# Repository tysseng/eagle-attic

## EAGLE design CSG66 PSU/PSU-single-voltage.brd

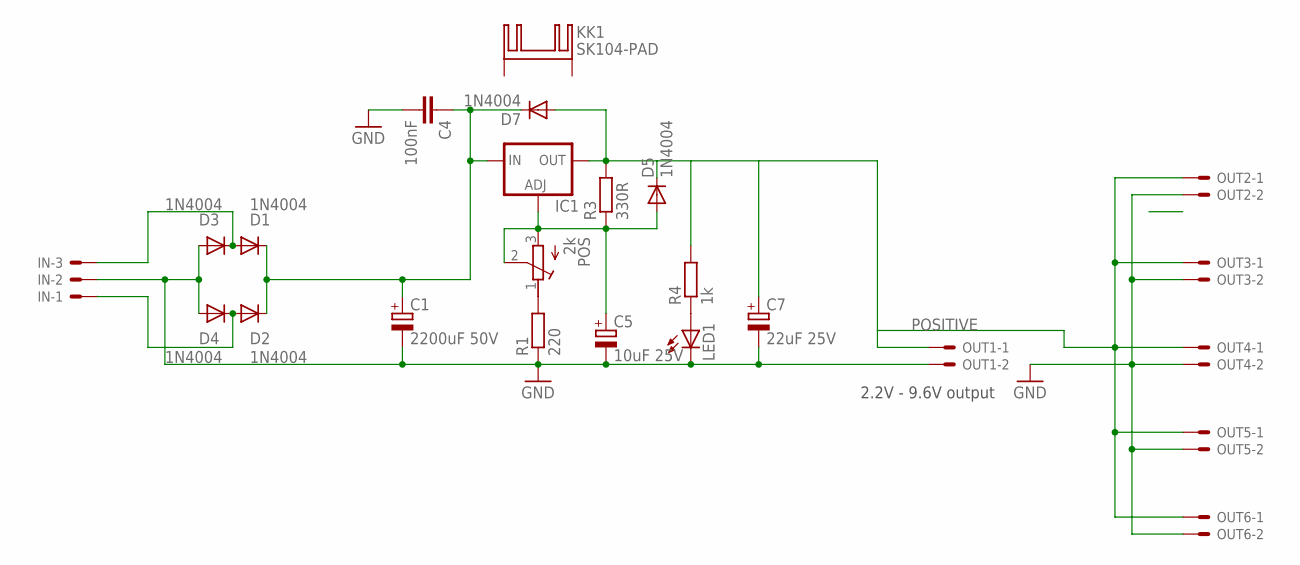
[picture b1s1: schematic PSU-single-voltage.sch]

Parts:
C1: 2200uF 50V; E7,5-16
C4: 100nF; C050-025X075
C5: 10uF 25V; E2,5-5
C7: 22uF 25V; E2,5-5
D1, D2, D3, D4, D5, D7: 1N4004; DO41-10
IC1: LM317TS; 317TS
IN: KK-156-3
KK1: SK104-PAD
LED1: LED3MM
OUT1, OUT2, OUT3, OUT4, OUT5, OUT6: KK-156-2
POS: 2k; RTRIMT93YA
R1: 220; 0207/7
R3: 330R; 0207/7
R4: 1k; 0207/7

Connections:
GND: C1.-, C4.2, C5.-, C7.-, D3.A, D4.A, IN.2, LED1.K (C), OUT1.2, OUT2.2, OUT3.2, OUT4.2, OUT5.2, OUT6.2, R1.1
unnamed: D2.A, D4.C, IN.1
unnamed: LED1.A, R4.1
unnamed: POS.1 (E), R1.2
unnamed: C5.+, D5.A, IC1.1 (ADJ), POS.2 (S), POS.3 (A), R3.1
unnamed: C1.+, C4.1, D1.C, D2.C, D7.C, IC1.3 (IN)
unnamed: D1.A, D3.C, IN.3
POSITIVE: C7.+, D5.C, D7.A, IC1.2 (OUT), OUT1.1, OUT2.1, OUT3.1, OUT4.1, OUT5.1, OUT6.1, R3.2, R4.2

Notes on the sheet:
2.2V - 9.6V output

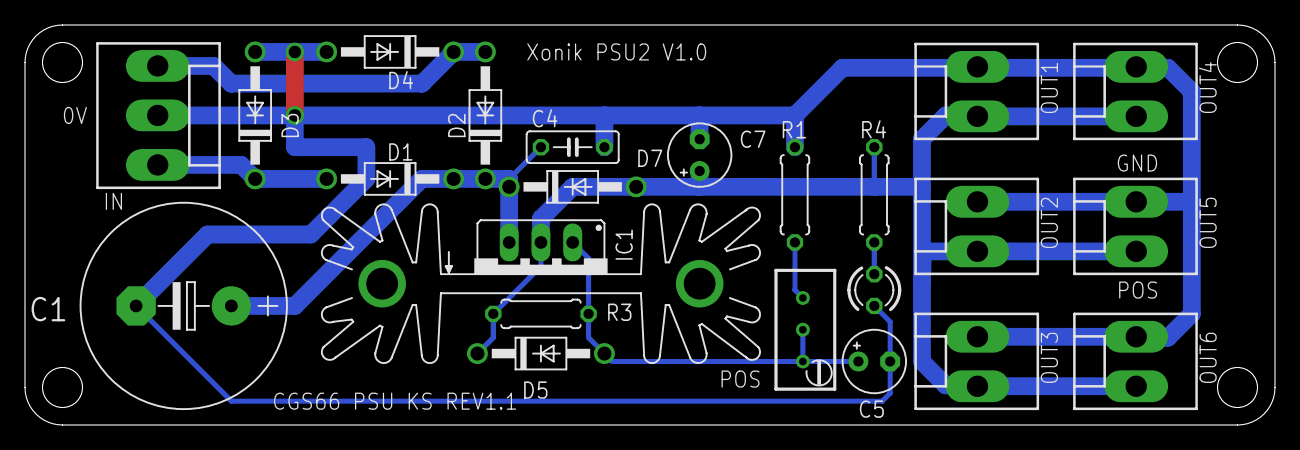
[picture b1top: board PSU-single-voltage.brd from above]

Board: 2 copper layers, 100.0 x 32.0 mm, 24 parts (0 on the bottom side), 8 nets.

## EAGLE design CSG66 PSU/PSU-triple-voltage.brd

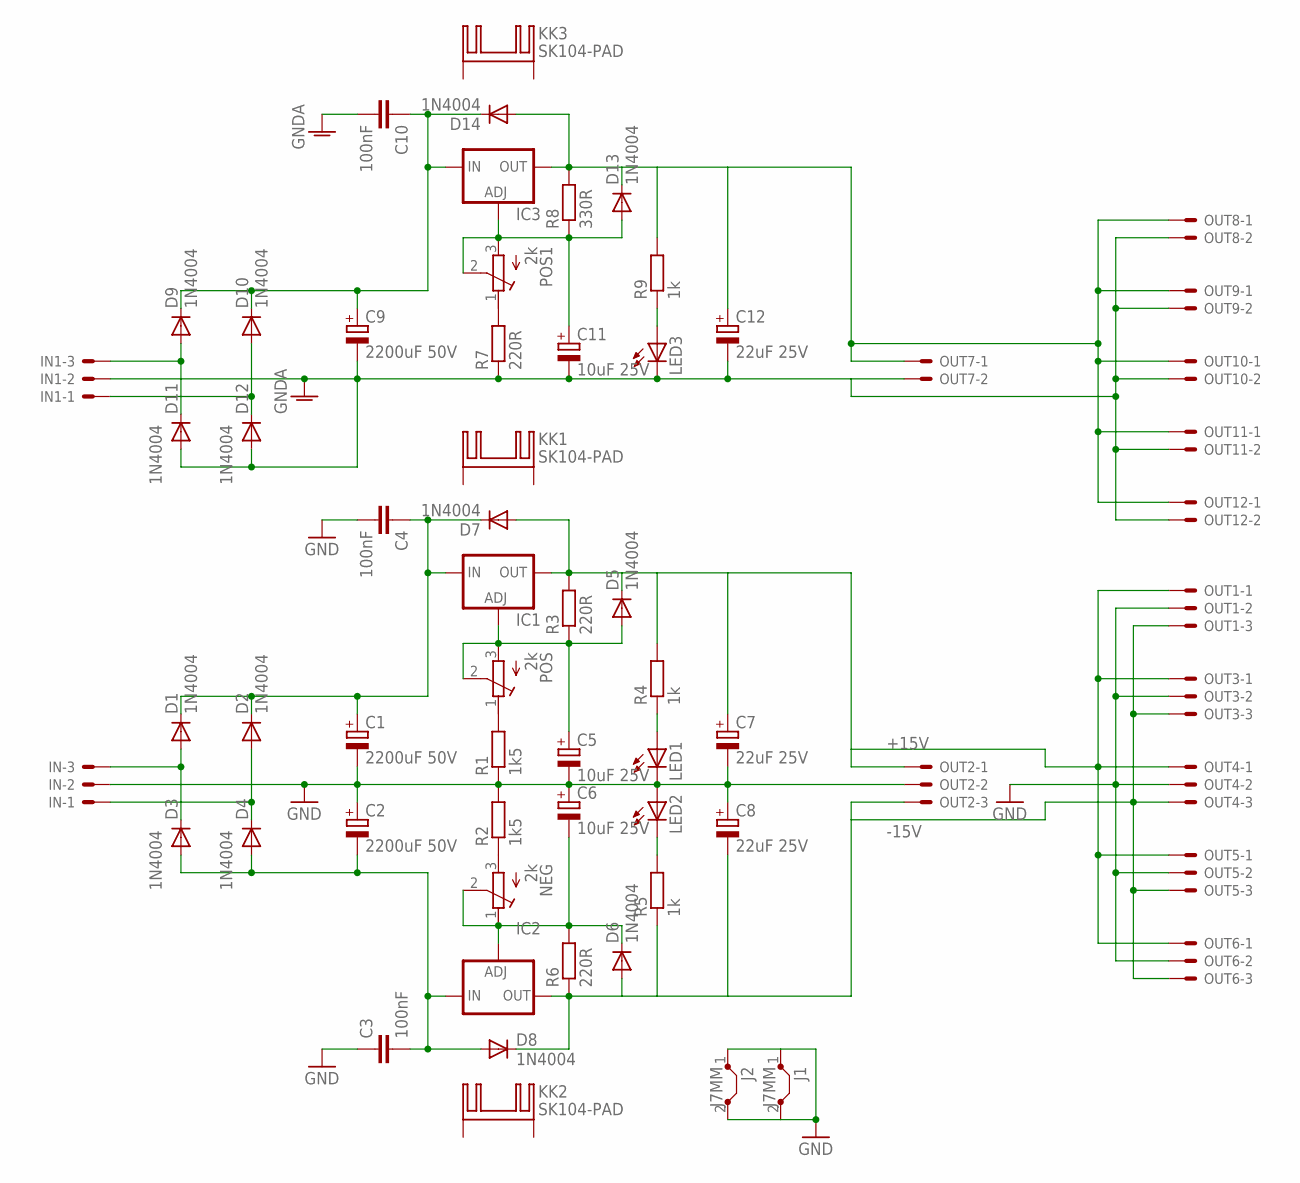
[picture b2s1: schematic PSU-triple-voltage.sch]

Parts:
C1, C2, C9: 2200uF 50V; E7,5-16
C3, C4, C10: 100nF; C050-025X075
C5, C6, C11: 10uF 25V; E2,5-5
C7, C8, C12: 22uF 25V; E2,5-5
D1, D2, D3, D4, D5, D6, D7, D8, D9, D10, D11, D12, D13, D14: 1N4004; DO41-10
IC1, IC3: LM317TS; 317TS
IC2: LM337TS; 337TS
IN, IN1: KK-156-3
J1, J2: J7MM; 07
KK1, KK2, KK3: SK104-PAD
LED1, LED2, LED3: LED3MM
NEG: 2k; RTRIMT93YA
OUT1, OUT2, OUT3, OUT4, OUT5, OUT6: KK-156-3
OUT7, OUT8, OUT9, OUT10, OUT11, OUT12: KK-156-2
POS, POS1: 2k; RTRIMT93YA
R1, R2: 1k5; 0207/7
R3, R6, R7: 220R; 0207/7
R4, R5, R9: 1k; 0207/7
R8: 330R; 0207/7

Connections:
+5V: C12.+, D13.C, D14.A, IC3.2 (OUT), OUT7.1, OUT8.1, OUT9.1, OUT10.1, OUT11.1, OUT12.1, R8.2, R9.2
+15V: C7.+, D5.C, D7.A, IC1.2 (OUT), OUT1.1, OUT2.1, OUT3.1, OUT4.1, OUT5.1, OUT6.1, R3.2, R4.2
-15V: C8.-, D6.A, D8.C, IC2.3 (OUT), OUT1.3, OUT2.3, OUT3.3, OUT4.3, OUT5.3, OUT6.3, R5.1, R6.1
GND: C1.-, C2.+, C3.1, C4.2, C5.-, C6.+, C7.-, C8.+, IN.2, J1.1, J1.2, J2.1, J2.2, LED1.K (C), LED2.A, OUT1.2, OUT2.2, OUT3.2, OUT4.2, OUT5.2, OUT6.2, R1.1, R2.2
GNDA: C9.-, C10.2, C11.-, C12.-, D11.A, D12.A, IN1.2, LED3.K (C), OUT7.2, OUT8.2, OUT9.2, OUT10.2, OUT11.2, OUT12.2, R7.1
unnamed: LED3.A, R9.1
unnamed: POS1.1 (E), R7.2
unnamed: C11.+, D13.A, IC3.1 (ADJ), POS1.2 (S), POS1.3 (A), R8.1
unnamed: LED1.A, R4.1
unnamed: C9.+, C10.1, D9.C, D10.C, D14.C, IC3.3 (IN)
unnamed: LED2.K (C), R5.2
unnamed: D10.A, D12.C, IN1.1
unnamed: POS.1 (E), R1.2
unnamed: C5.+, D5.A, IC1.1 (ADJ), POS.2 (S), POS.3 (A), R3.1
unnamed: NEG.3 (A), R2.1
unnamed: C6.-, D6.C, IC2.1 (ADJ), NEG.1 (E), NEG.2 (S), R6.2
unnamed: C2.-, C3.2, D3.A, D4.A, D8.A, IC2.2 (IN)
unnamed: D9.A, D11.C, IN1.3
unnamed: C1.+, C4.1, D1.C, D2.C, D7.C, IC1.3 (IN)
unnamed: D2.A, D4.C, IN.1
unnamed: D1.A, D3.C, IN.3

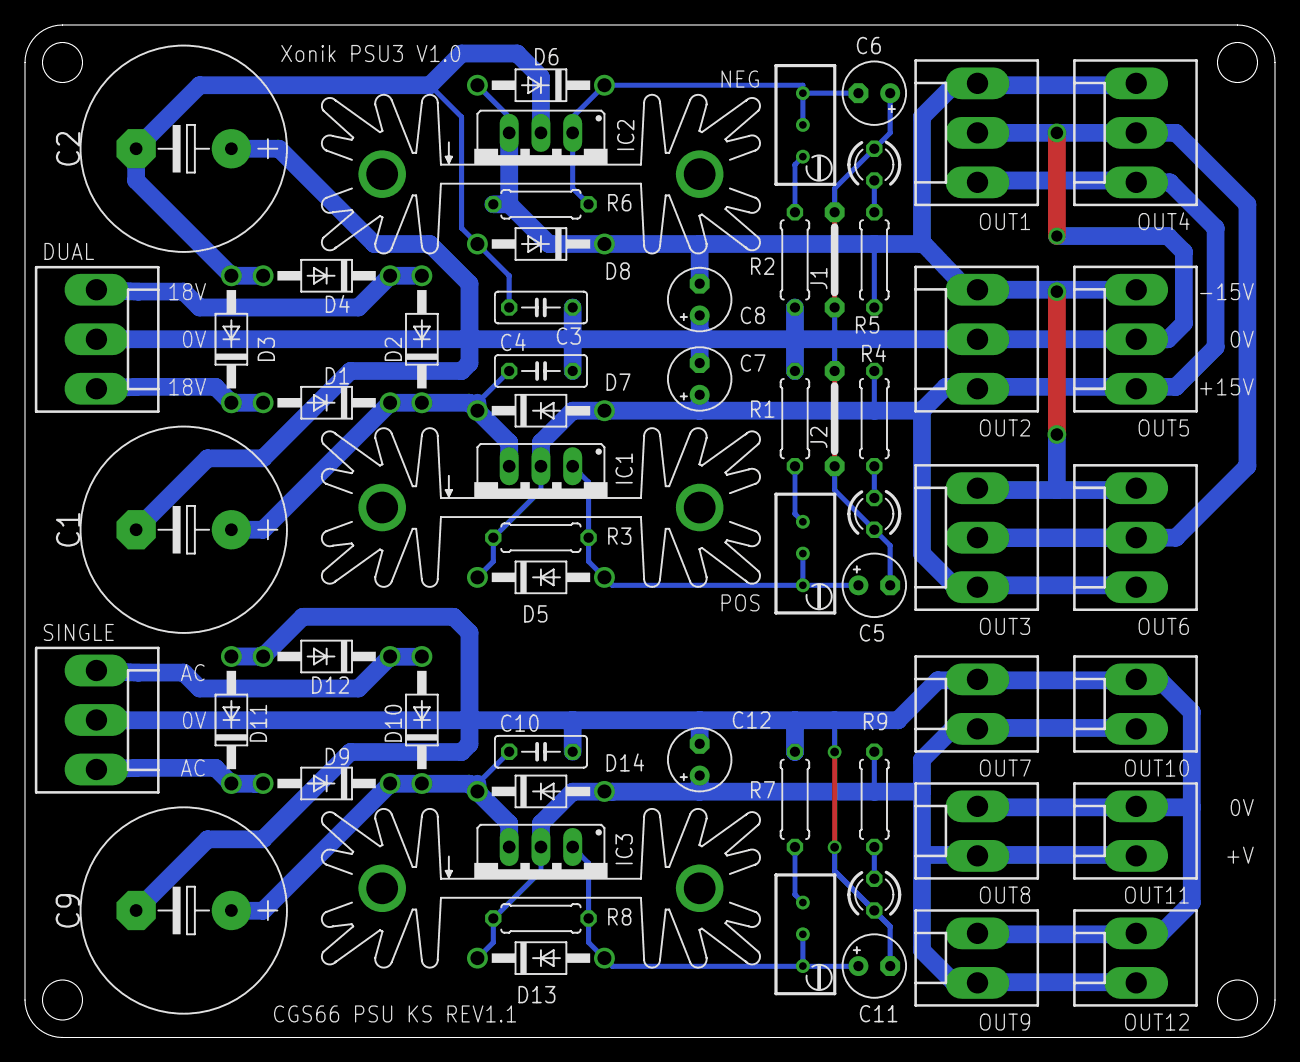
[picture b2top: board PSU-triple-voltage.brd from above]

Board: 2 copper layers, 100.0 x 81.0 mm, 63 parts (0 on the bottom side), 21 nets.

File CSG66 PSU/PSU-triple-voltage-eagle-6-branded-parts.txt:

Partlist

Exported from PSU-triple-voltage-eagle-6-branded.sch at 01.03.2015 13:05:13

EAGLE Version 6.2.0 Copyright (c) 1988-2012 CadSoft

Assembly variant: 

Part     Value          Device          Package      Library   Sheet

C1       2200uF 50V     CPOL-EUE7.5-16  E7,5-16      resistor  1
C2       2200uF 50V     CPOL-EUE7.5-16  E7,5-16      resistor  1
C3       100nF          C-EU050-025X075 C050-025X075 resistor  1
C4       100nF          C-EU050-025X075 C050-025X075 resistor  1
C5       10uF 25V       CPOL-EUE2.5-5   E2,5-5       resistor  1
C6       10uF 25V       CPOL-EUE2.5-5   E2,5-5       resistor  1
C7       22uF 25V       CPOL-EUE2.5-5   E2,5-5       resistor  1
C8       22uF 25V       CPOL-EUE2.5-5   E2,5-5       resistor  1
C9       2200uF 50V     CPOL-EUE7.5-16  E7,5-16      resistor  1
C10      100nF          C-EU050-025X075 C050-025X075 resistor  1
C11      10uF 25V       CPOL-EUE2.5-5   E2,5-5       resistor  1
C12      22uF 25V       CPOL-EUE2.5-5   E2,5-5       resistor  1
D1       1N4004         1N4004          DO41-10      diode     1
D2       1N4004         1N4004          DO41-10      diode     1
D3       1N4004         1N4004          DO41-10      diode     1
D4       1N4004         1N4004          DO41-10      diode     1
D5       1N4004         1N4004          DO41-10      diode     1
D6       1N4004         1N4004          DO41-10      diode     1
D7       1N4004         1N4004          DO41-10      diode     1
D8       1N4004         1N4004          DO41-10      diode     1
D9       1N4004         1N4004          DO41-10      diode     1
D10      1N4004         1N4004          DO41-10      diode     1
D11      1N4004         1N4004          DO41-10      diode     1
D12      1N4004         1N4004          DO41-10      diode     1
D13      1N4004         1N4004          DO41-10      diode     1
D14      1N4004         1N4004          DO41-10      diode     1
IC1                     LM317TS         317TS        v-reg     1
IC2                     LM337TS         337TS        v-reg     1
IC3                     LM317TS         317TS        v-reg     1
IN                      KK-156-3        KK-156-3     con-molex 1
IN1                     KK-156-3        KK-156-3     con-molex 1
KK1      SK104-PAD      SK104-PAD       SK104-PAD    heatsink  1
KK2      SK104-PAD      SK104-PAD       SK104-PAD    heatsink  1
KK3      SK104-PAD      SK104-PAD       SK104-PAD    heatsink  1
LED1                    LED3MM          LED3MM       led       1
LED2                    LED3MM          LED3MM       led       1
LED3                    LED3MM          LED3MM       led       1
NEG      2k             R-TRIMMT93YA    RTRIMT93YA   resistor  1
OUT1                    KK-156-3        KK-156-3     con-molex 1
OUT2                    KK-156-3        KK-156-3     con-molex 1
OUT3                    KK-156-3        KK-156-3     con-molex 1
OUT4                    KK-156-3        KK-156-3     con-molex 1
OUT5                    KK-156-3        KK-156-3     con-molex 1
OUT6                    KK-156-3        KK-156-3     con-molex 1
OUT7                    KK-156-2        KK-156-2     con-molex 1
OUT8                    KK-156-2        KK-156-2     con-molex 1
OUT9                    KK-156-2        KK-156-2     con-molex 1
OUT10                   KK-156-2        KK-156-2     con-molex 1
OUT11                   KK-156-2        KK-156-2     con-molex 1
OUT12                   KK-156-2        KK-156-2     con-molex 1
POS      2k             R-TRIMMT93YA    RTRIMT93YA   resistor  1
POS1     2k             R-TRIMMT93YA    RTRIMT93YA   resistor  1
R1       1k5            R-EU_0207/7     0207/7       resistor  1
R2       1k5            R-EU_0207/7     0207/7       resistor  1
R3       220R           R-EU_0207/7     0207/7       resistor  1
R4       1k             R-EU_0207/7     0207/7       resistor  1
R5       1k             R-EU_0207/7     0207/7       resistor  1
R6       220R           R-EU_0207/7     0207/7       resistor  1
R7       220R           R-EU_0207/7     0207/7       resistor  1
R8       330R           R-EU_0207/7     0207/7       resistor  1
R9       1k             R-EU_0207/7     0207/7       resistor  1

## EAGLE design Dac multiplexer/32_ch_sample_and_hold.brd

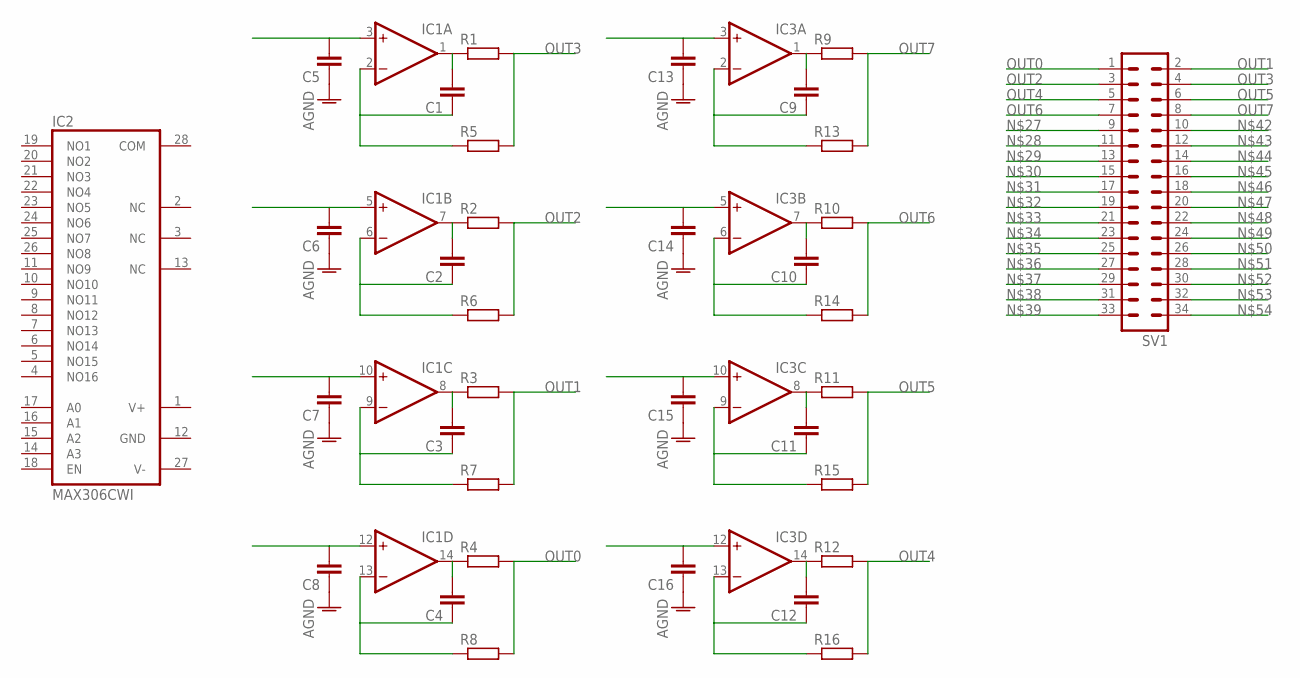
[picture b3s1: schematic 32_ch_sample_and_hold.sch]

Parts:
C1, C2, C3, C4, C9, C10, C11, C12: C-EUC0603; C0603
C5, C6, C7, C8, C13, C14, C15, C16: C-EUC1206; C1206
IC1, IC3: TL074D; SO14
IC2: MAX306CWI; SO28L
R1, R2, R3, R4, R5, R6, R7, R8, R9, R10, R11, R12, R13, R14, R15, R16: R-EU_R0603; R0603
SV1: MA17-2

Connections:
AGND: C5.1, C6.1, C7.1, C8.1, C13.1, C14.1, C15.1, C16.1
GND: IC2.12 (GND)
unnamed: C1.2, IC1.1 (OUT), R1.1
unnamed: C2.2, IC1.7 (OUT), R2.1
unnamed: C3.2, IC1.8 (OUT), R3.1
unnamed: C4.2, IC1.14 (OUT), R4.1
unnamed: C1.1, IC1.2 (-IN), R5.1
unnamed: C2.1, IC1.6 (-IN), R6.1
unnamed: C3.1, IC1.9 (-IN), R7.1
unnamed: C4.1, IC1.13 (-IN), R8.1
unnamed: C9.2, IC3.1 (OUT), R9.1
unnamed: C10.2, IC3.7 (OUT), R10.1
unnamed: C11.2, IC3.8 (OUT), R11.1
unnamed: C12.2, IC3.14 (OUT), R12.1
unnamed: C8.2, IC1.12 (+IN)
unnamed: C7.2, IC1.10 (+IN)
unnamed: C6.2, IC1.5 (+IN)
unnamed: C5.2, IC1.3 (+IN)
unnamed: C9.1, IC3.2 (-IN), R13.1
unnamed: C10.1, IC3.6 (-IN), R14.1
unnamed: C11.1, IC3.9 (-IN), R15.1
unnamed: C12.1, IC3.13 (-IN), R16.1
unnamed: C16.2, IC3.12 (+IN)
unnamed: C15.2, IC3.10 (+IN)
unnamed: C14.2, IC3.5 (+IN)
unnamed: C13.2, IC3.3 (+IN)
OUT0: R4.2, R8.2, SV1.1
OUT1: R3.2, R7.2, SV1.2
OUT2: R2.2, R6.2, SV1.3
OUT3: R1.2, R5.2, SV1.4
OUT4: R12.2, R16.2, SV1.5
OUT5: R11.2, R15.2, SV1.6
OUT6: R10.2, R14.2, SV1.7
OUT7: R9.2, R13.2, SV1.8
V+: IC1.4 (V+), IC2.1 (V+), IC3.4 (V+)
V-: IC1.11 (V-), IC2.27 (V-), IC3.11 (V-)

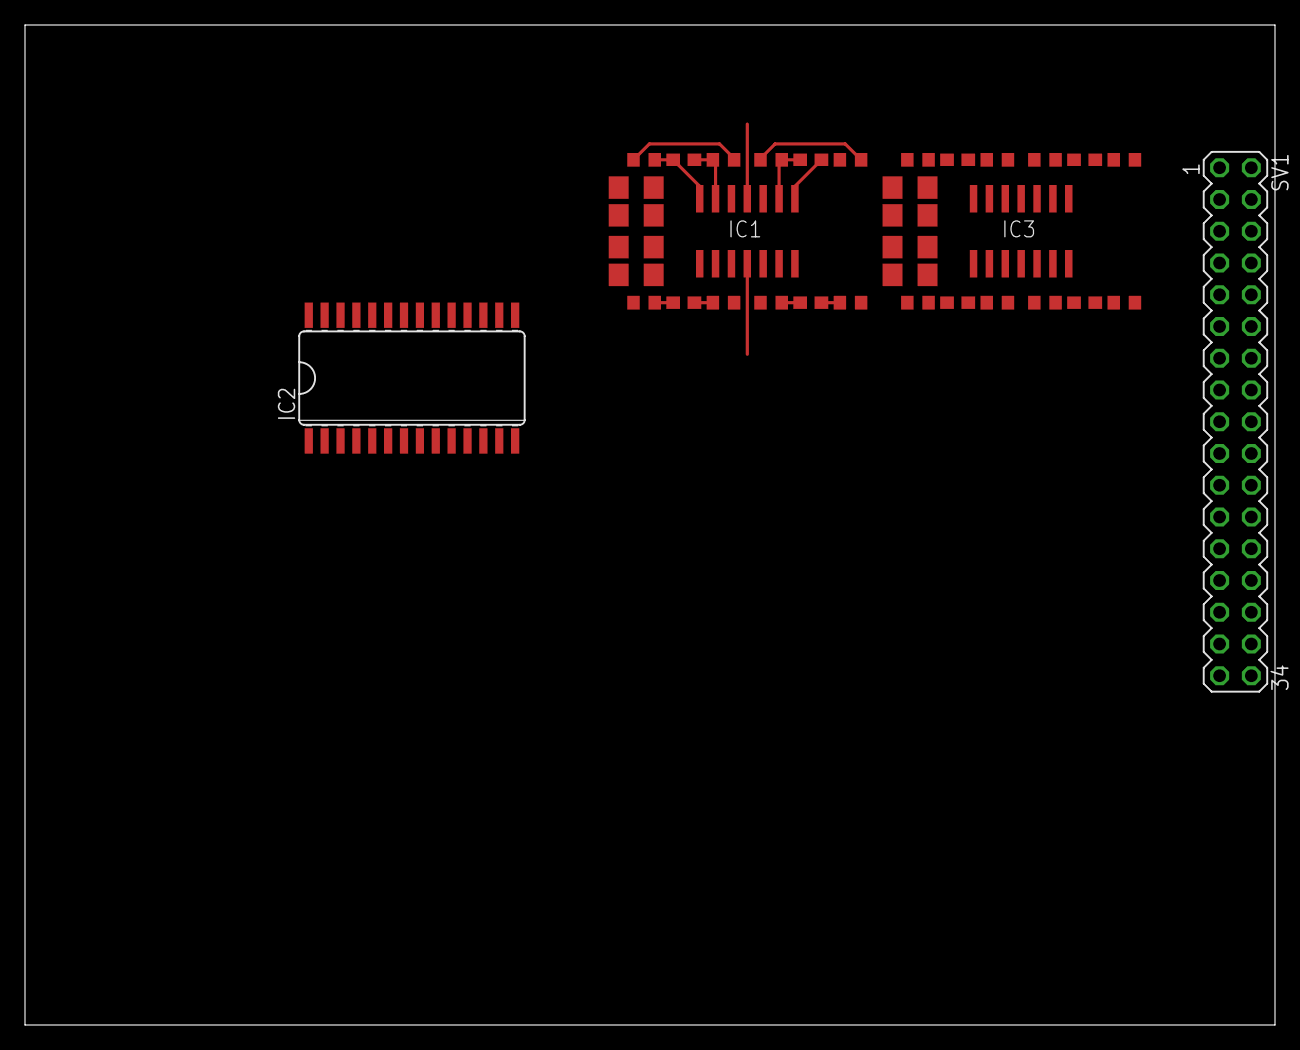
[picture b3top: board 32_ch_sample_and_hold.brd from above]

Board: 2 copper layers, 100.0 x 80.0 mm, 36 parts (0 on the bottom side), 35 nets.

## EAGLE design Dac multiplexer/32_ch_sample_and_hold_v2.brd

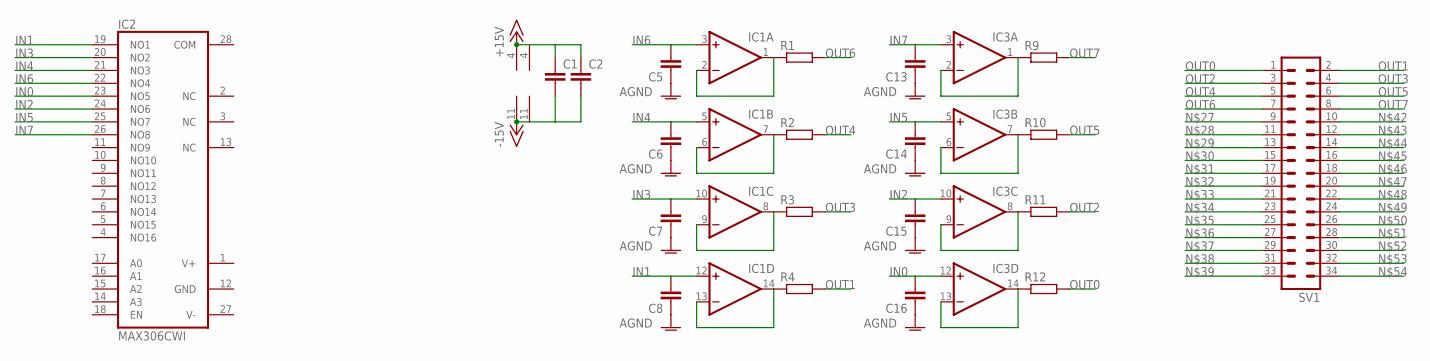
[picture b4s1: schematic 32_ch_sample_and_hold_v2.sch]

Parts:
C1, C2: C-EUC0603; C0603
C5, C6, C7, C8, C13, C14, C15, C16: C-EUC1206; C1206
IC1, IC3: TL074D; SO14
IC2: MAX306CWI; SO28L
R1, R2, R3, R4, R9, R10, R11, R12: R-EU_R0603; R0603
SV1: MA17-2

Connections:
+15V: C1.1, C2.1, IC1.4 (V+), IC3.4 (V+)
-15V: C1.2, C2.2, IC1.11 (V-), IC3.11 (V-)
AGND: C5.1, C6.1, C7.1, C8.1, C13.1, C14.1, C15.1, C16.1
GND: IC2.12 (GND)
IN0: C16.2, IC2.23 (NO5), IC3.12 (+IN)
IN1: C8.2, IC1.12 (+IN), IC2.19 (NO1)
IN2: C15.2, IC2.24 (NO6), IC3.10 (+IN)
IN3: C7.2, IC1.10 (+IN), IC2.20 (NO2)
IN4: C6.2, IC1.5 (+IN), IC2.21 (NO3)
IN5: C14.2, IC2.25 (NO7), IC3.5 (+IN)
IN6: C5.2, IC1.3 (+IN), IC2.22 (NO4)
IN7: C13.2, IC2.26 (NO8), IC3.3 (+IN)
unnamed: IC1.1 (OUT), IC1.2 (-IN), R1.1
unnamed: IC1.6 (-IN), IC1.7 (OUT), R2.1
unnamed: IC1.8 (OUT), IC1.9 (-IN), R3.1
unnamed: IC1.13 (-IN), IC1.14 (OUT), R4.1
unnamed: IC3.1 (OUT), IC3.2 (-IN), R9.1
unnamed: IC3.6 (-IN), IC3.7 (OUT), R10.1
unnamed: IC3.8 (OUT), IC3.9 (-IN), R11.1
unnamed: IC3.13 (-IN), IC3.14 (OUT), R12.1
OUT0: R12.2, SV1.1
OUT1: R4.2, SV1.2
OUT2: R11.2, SV1.3
OUT3: R3.2, SV1.4
OUT4: R2.2, SV1.5
OUT5: R10.2, SV1.6
OUT6: R1.2, SV1.7
OUT7: R9.2, SV1.8
V+: IC2.1 (V+)
V-: IC2.27 (V-)

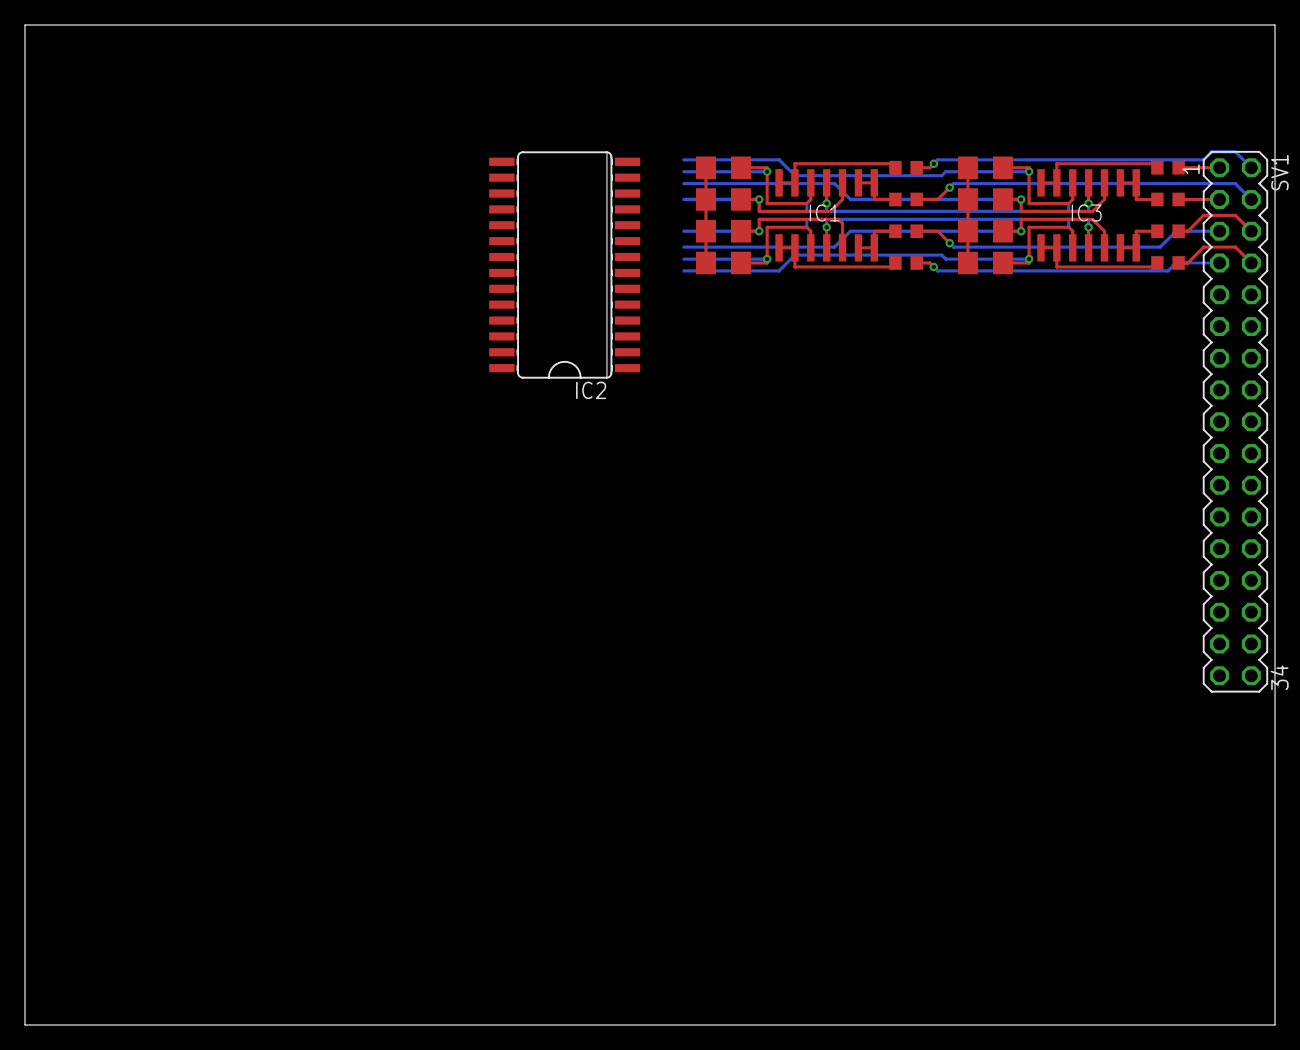
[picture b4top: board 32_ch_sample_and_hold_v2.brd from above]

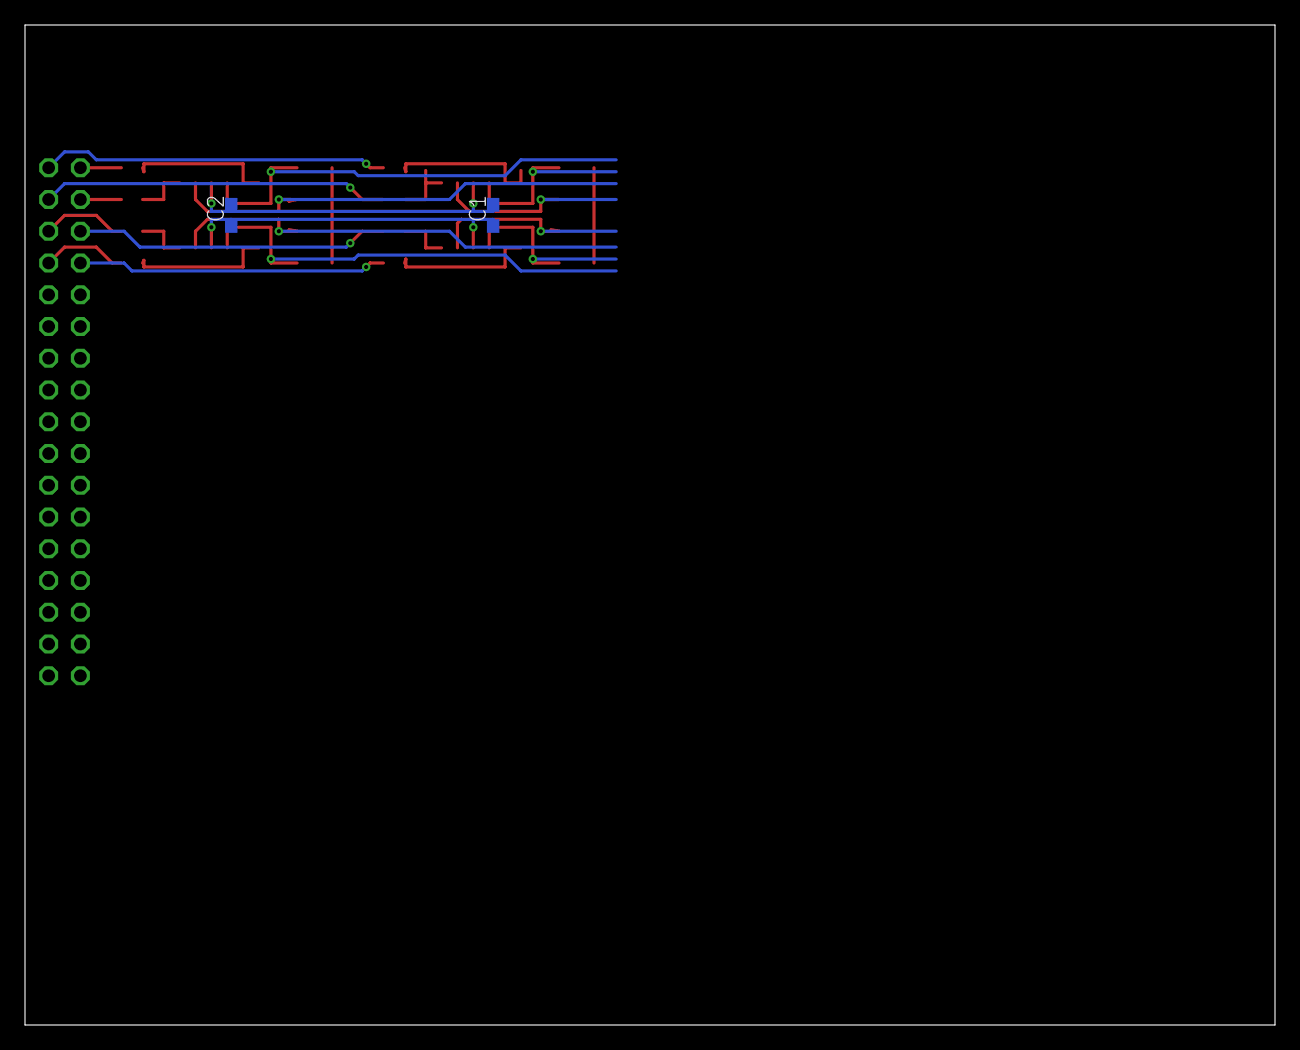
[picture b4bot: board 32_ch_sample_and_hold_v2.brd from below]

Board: 2 copper layers, 100.0 x 80.0 mm, 22 parts (2 on the bottom side), 27 nets.

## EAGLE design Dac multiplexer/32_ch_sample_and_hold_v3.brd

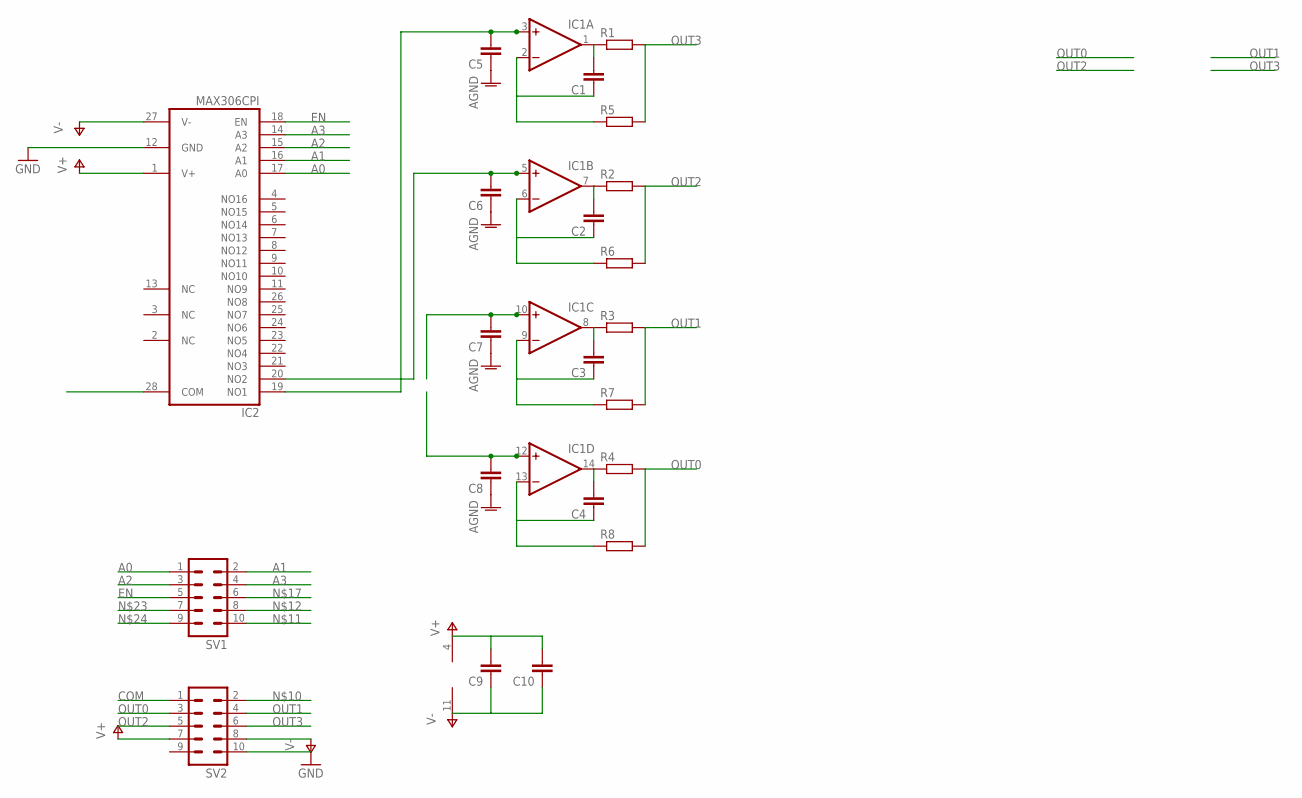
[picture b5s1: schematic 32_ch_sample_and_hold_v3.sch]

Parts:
C1, C2, C3, C4, C5, C6, C7, C8, C9, C10: C-EU025-025X050; C025-025X050
IC1: TL074P; DIL14
IC2: MAX306CPI; DIL28-6
R1, R2, R3, R4, R5, R6, R7, R8: R-EU_0207/7; 0207/7
SV1, SV2: MA05-2

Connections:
A0: IC2.17 (A0), SV1.1
A1: IC2.16 (A1), SV1.2
A2: IC2.15 (A2), SV1.3
A3: IC2.14 (A3), SV1.4
AGND: C5.1, C6.1, C7.1, C8.1
COM: IC2.28 (COM), SV2.1
EN: IC2.18 (EN), SV1.5
GND: IC2.12 (GND), SV2.10
unnamed: C1.2, IC1.1 (OUT), R1.1
unnamed: C2.2, IC1.7 (OUT), R2.1
unnamed: C3.2, IC1.8 (OUT), R3.1
unnamed: C4.2, IC1.14 (OUT), R4.1
unnamed: C1.1, IC1.2 (-IN), R5.1
unnamed: C2.1, IC1.6 (-IN), R6.1
unnamed: C3.1, IC1.9 (-IN), R7.1
unnamed: C4.1, IC1.13 (-IN), R8.1
unnamed: C8.2, IC1.12 (+IN)
unnamed: C7.2, IC1.10 (+IN)
unnamed: C6.2, IC1.5 (+IN), IC2.20 (NO2)
unnamed: C5.2, IC1.3 (+IN), IC2.19 (NO1)
OUT0: R4.2, R8.2, SV2.3
OUT1: R3.2, R7.2, SV2.4
OUT2: R2.2, R6.2, SV2.5
OUT3: R1.2, R5.2, SV2.6
V+: C9.2, C10.2, IC1.4 (V+), IC2.1 (V+), SV2.7
V-: C9.1, C10.1, IC1.11 (V-), IC2.27 (V-), SV2.8

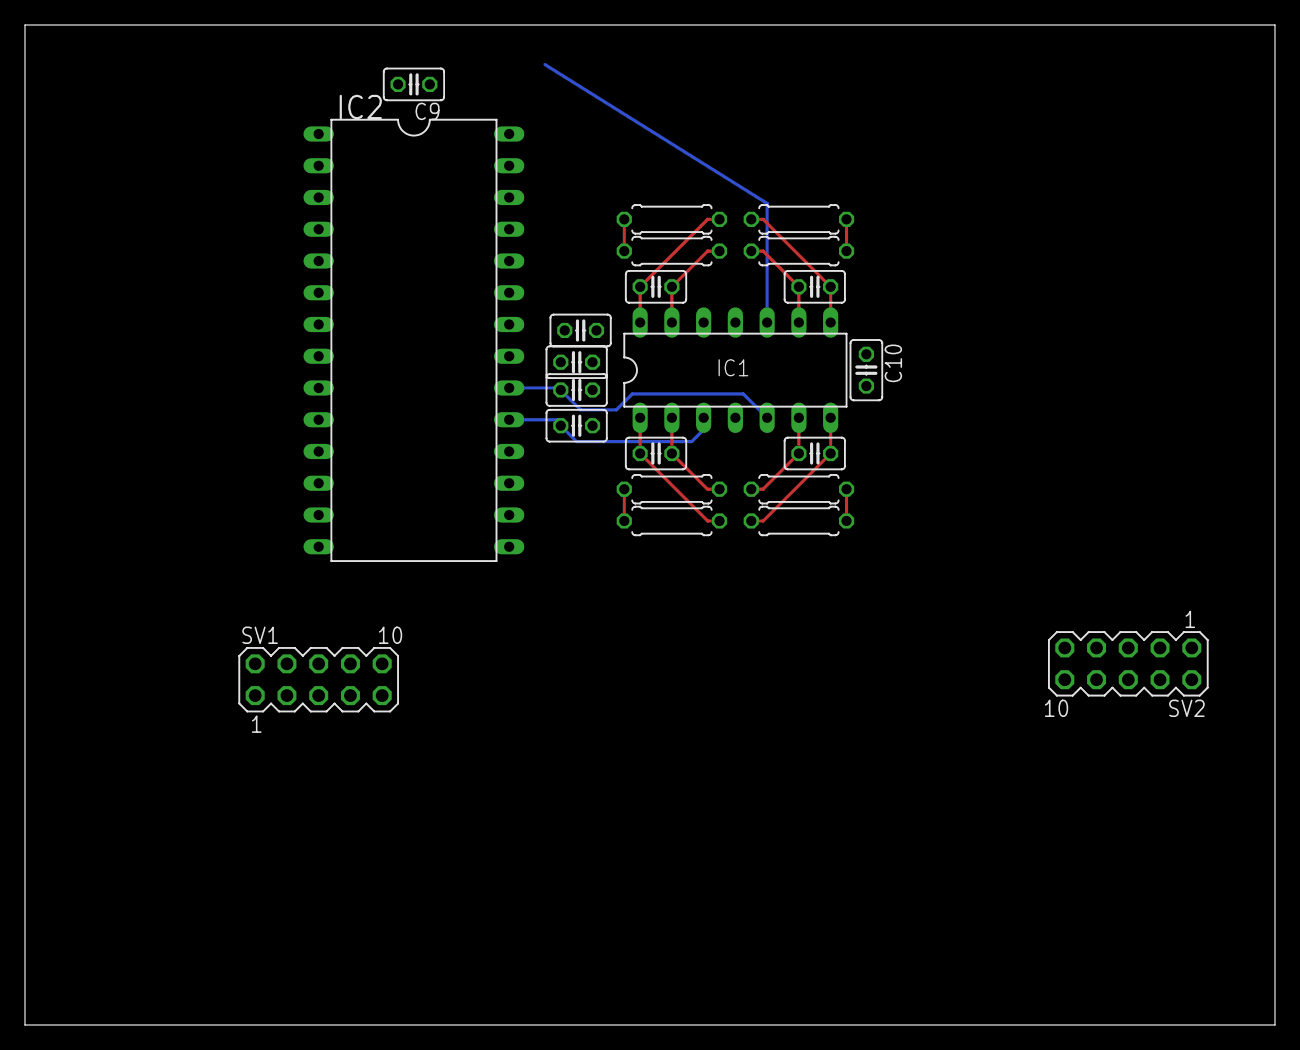
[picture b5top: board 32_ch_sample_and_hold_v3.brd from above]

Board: 2 copper layers, 100.0 x 80.0 mm, 22 parts (0 on the bottom side), 26 nets.
